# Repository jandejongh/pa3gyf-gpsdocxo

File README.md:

# pa3gyf-gpsdocxo
GPS-Disciplined OCXO

After (a.o.) G3RUH and G4HUP, with PA3GYF additions for monitoring GPS (FIX) status, extra isolation of the (sine) output signals from the PLL, monitoring OCXO heater, monitoring PLL LOCK status, manual frequency tuning (stand-alone OCXO) and stand-alone GPS operation.
Includes front and rear panel designs (Schaeffer Front-Panel Designer) and Arduino firmware,
both for Arduino Uno and Arduino Micro.

## Background

At around 2016, I decided to pick up my RF electronics and HAM hobby again after a decade (at least) absence,
and I decided to build a GPS-disciplined OCXO in order to regain lost skills.
I wanted a precision frequency reference and had struggled for years with a DCF77 circuit that never
seemed to lock. As I was able to purchase a large amount of (HP) test equipment (around 2013),
a stable frequency reference turned out to be the ideal restart project for me.

I designed and built most of the circuit in 2016 and early 2017, but never took the time to
properly test and document it. As an autumn 2019 winter project, I finished latest testing and modifications,
wrote the documentation
and submitted everything to github (before that, the repo contained photos only).

## Credits

The core design of this project, the PLL circuitry including the loop filter, was shamelessly stolen
from G3RUH; the distribution amplifier is an unmodified unit (bought) from G4HUP.

My main (modest) contributions have been the extension of the core design with monitoring and control functions,
such as monitoring whether or not the GPS receiver has a fix,
monitoring the lock status of the PLL,
RS-232C interfacing to the GPS receiver,
front-panel and rear-panel designs,
and Arduino firmware code, including an algorithm for deciding upon PLL-lock
from monitoring the OCXO tune voltage.

In addition, I changed (improved?) the interfacing between the OCXO and the PLL by
introducing an isolator for separation of the PLL and output signals from the OCXO,
and designed and implemented a Low-Noise Amplifier for the OCXO signal in case (well, almost always)
the OCXO is insufficient to properly activate the Schmitt-Triggers of the PLL circuit.

My explicit thank-yous to Frank van Vliet for his interest in this project.

## Structure of the Repository

The repository is organized as follows:
- doc:           Contains documentation; mandatory reading (in particular the 'manual')
                   if you want to rebuilt this project,
                   or use it as a basis for your own design.
                 Most if not all documentation is written with OpenOffice,
                   but I try to keep a set of PDFs in sync,
                   for those that cannot use OpenOffice.
- fpd:           Contains the front and rear panel designs (for Schaeffer, www.schaeffer-ag.de, front-panel designer).
- fw:            Contains the Arduino firmware; a single file for both Uno and Micro (compile-time switch!).
- pcb:           Contains the KiCAD PCB designs for this project.
                 The PCBs were originally designed in KiCAD v3 (well, some v3),
                   and I migrated the crucial ones (part of V1) to KiCAD v4.
- pcb/v1-kicad3: Contains the (original) KiCAD-V3xx PCB designs for all PCBs,
                   including earlier versions that had faults,
                   and including the ones for the Arduino Uno.
                 The KiCAD projects also contain a lot of 3D shape definitions.
- pcb/v1-kicad4: Contains the KiCAD-V4xx PCB designs for the essential PCBs in the V1 unit.
                 It is a subset of the pcb/v1-kicad3 KiCAD projects migrated to KiCAD V4.
                 It does not include previous PCB versions nor the Arduino Uno PCBs.
                 Also, it does not include most of the 3D shapes for the 3D view.
- transformer:   Contains details on the transformer used for the Power Supply Unit.
- enclosure:     Contains details on the Velleman enclosure (I) used.

## Conclusion

Designing and realizing this project has been a true joy!

## Future

Currently, my interest has somewhat shifted towards the accuracy of power reading of my equipment,
so I do not expect updates soon.

However, it is still on my wishlist to use an ADC with higher resolution and accuracy than the Arduino
10-bit circuits in order to assess PLL lock status.
Also, I want to study the PLL status by simply counting the pulses on both
inputs over varying intervals, in order to more accurately quantify the PLL locked status (e.g., 10-4 over
the last second, 10-6 over the past 10 minutes, 10-7 over the past hour, etc.).
I would also love to improve the RS232-C circuit in such a way that it can be used directly as an
input to Linux gpsd and ntp/chrony as a PPS-capable time source.
At the present time, this does not work.
Finally, I would love an Ethernet interface for monitoring and control of the unit.

Unfortunately, at the present time, two hurdles would need to be taken.
First, the availability of the required GPS receiver is (AFAICT) close to zero,
and I would have to switch to 1PPS use.
Second, the memory availability on the current Arduino models is really WAY TOO LOW.
I almost forgot what the K symbol means in a computer-memory context.

So, all in all, it might be better to wait for more powerful Arduino models,
and perhaps think of a 1 PPS design.

Who knows...

## License

All my parts, both hardware and software, have been released under Apache Commons License V2.

## 73

Jan (pa3gyf)

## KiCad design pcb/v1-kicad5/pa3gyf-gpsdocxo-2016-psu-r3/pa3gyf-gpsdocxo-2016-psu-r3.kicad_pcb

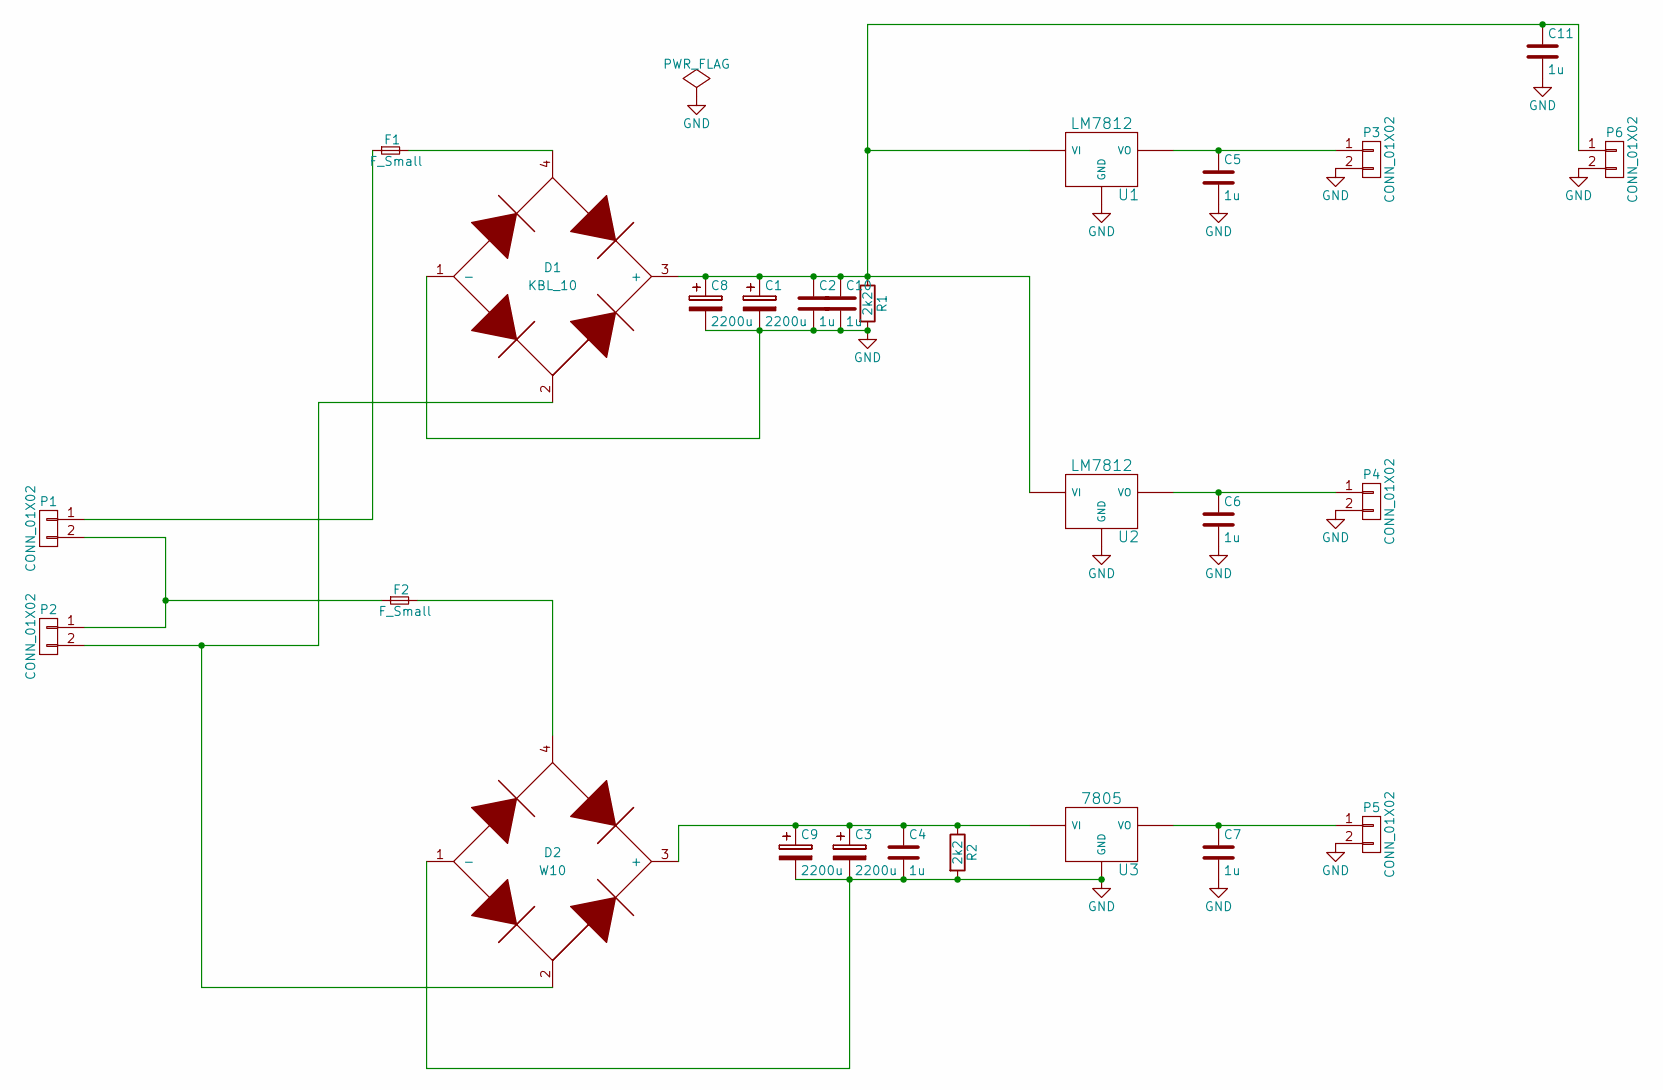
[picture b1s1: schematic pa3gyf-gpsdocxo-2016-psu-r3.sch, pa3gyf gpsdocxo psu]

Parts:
C1, C3, C8, C9: 2200u; Elko_vert_30x16mm_RM7.5
C2, C4, C5, C6, C7, C10, C11: 1u; C_0805_HandSoldering
D1: KBL_10; Bridge_KBL
D2: W10
F1, F2: F_Small; Fuseholder5x20_horiz_SemiClosed_Casing10x25mm
P1, P2, P3, P4, P5, P6: CONN_01X02; Weidmuller_GS5_2_2pin
R1, R2: 2k2; Resistor_Horizontal_RM15mm
U1, U2: LM7812; LM78XXV
U3: 7805; LM78XXV

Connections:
GND: C1.2, C2.2, C3.2, C4.2, C5.2, C6.2, C7.2, C8.2, C9.2, C10.2, C11.2, D1.1 (-), D2.1 (-), P3.2, P4.2, P5.2, P6.2, R1.2, R2.2, U1.GND, U2.GND, U3.GND
unnamed: C1.1, C2.1, C8.1, C10.1, C11.1, D1.3 (+), P6.1, R1.1, U1.VI, U2.VI
unnamed: C3.1, C4.1, C9.1, D2.3 (+), R2.1, U3.VI
unnamed: C5.1, P3.1, U1.VO
unnamed: C6.1, P4.1, U2.VO
unnamed: C7.1, P5.1, U3.VO
unnamed: D1.2, D2.2, P2.2
unnamed: D1.4, F1.2
unnamed: D2.4, F2.2
unnamed: F1.1, P1.1
unnamed: F2.1, P1.2, P2.1

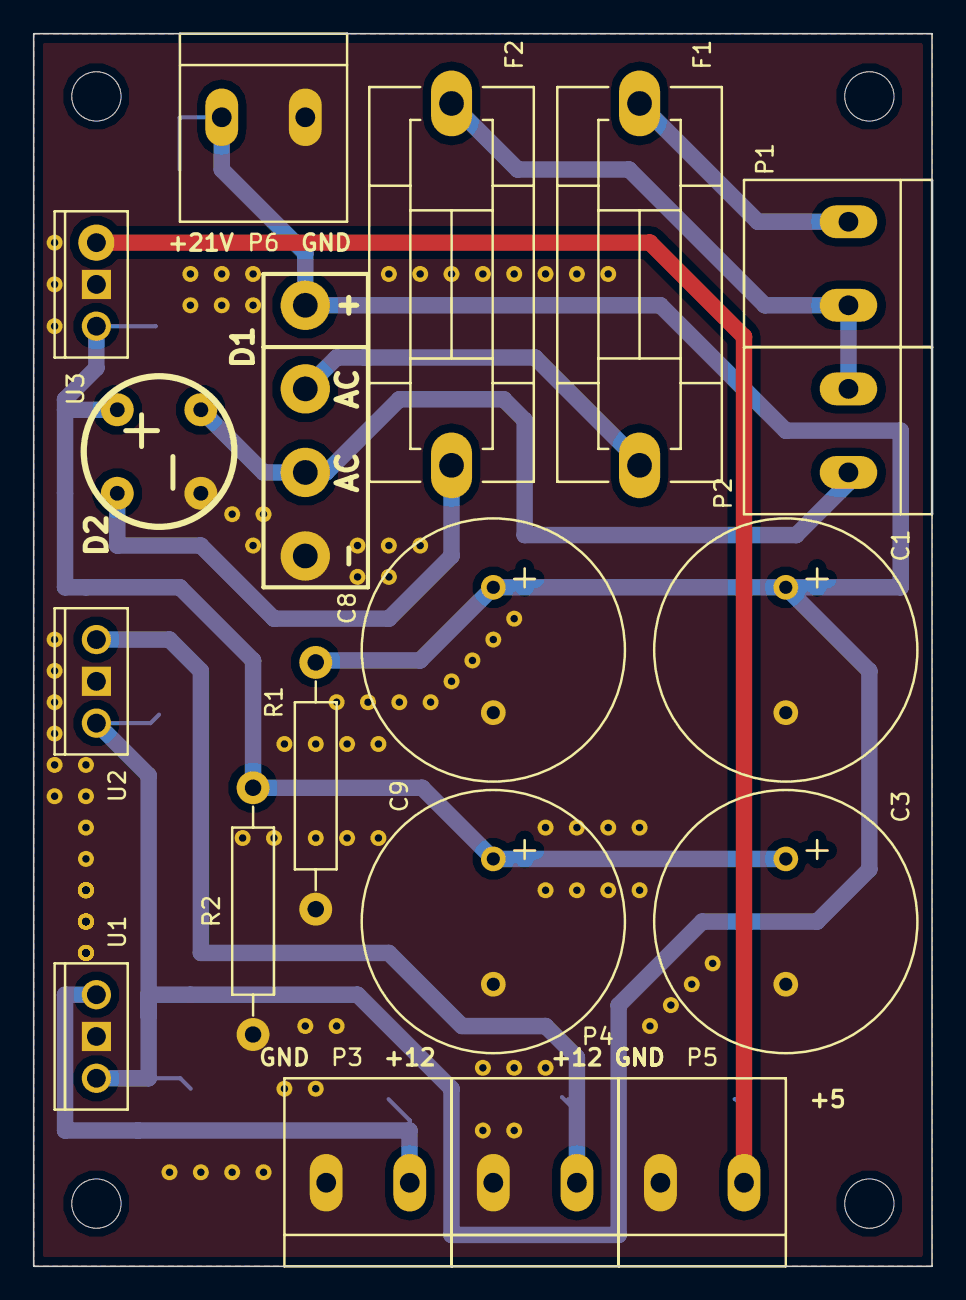
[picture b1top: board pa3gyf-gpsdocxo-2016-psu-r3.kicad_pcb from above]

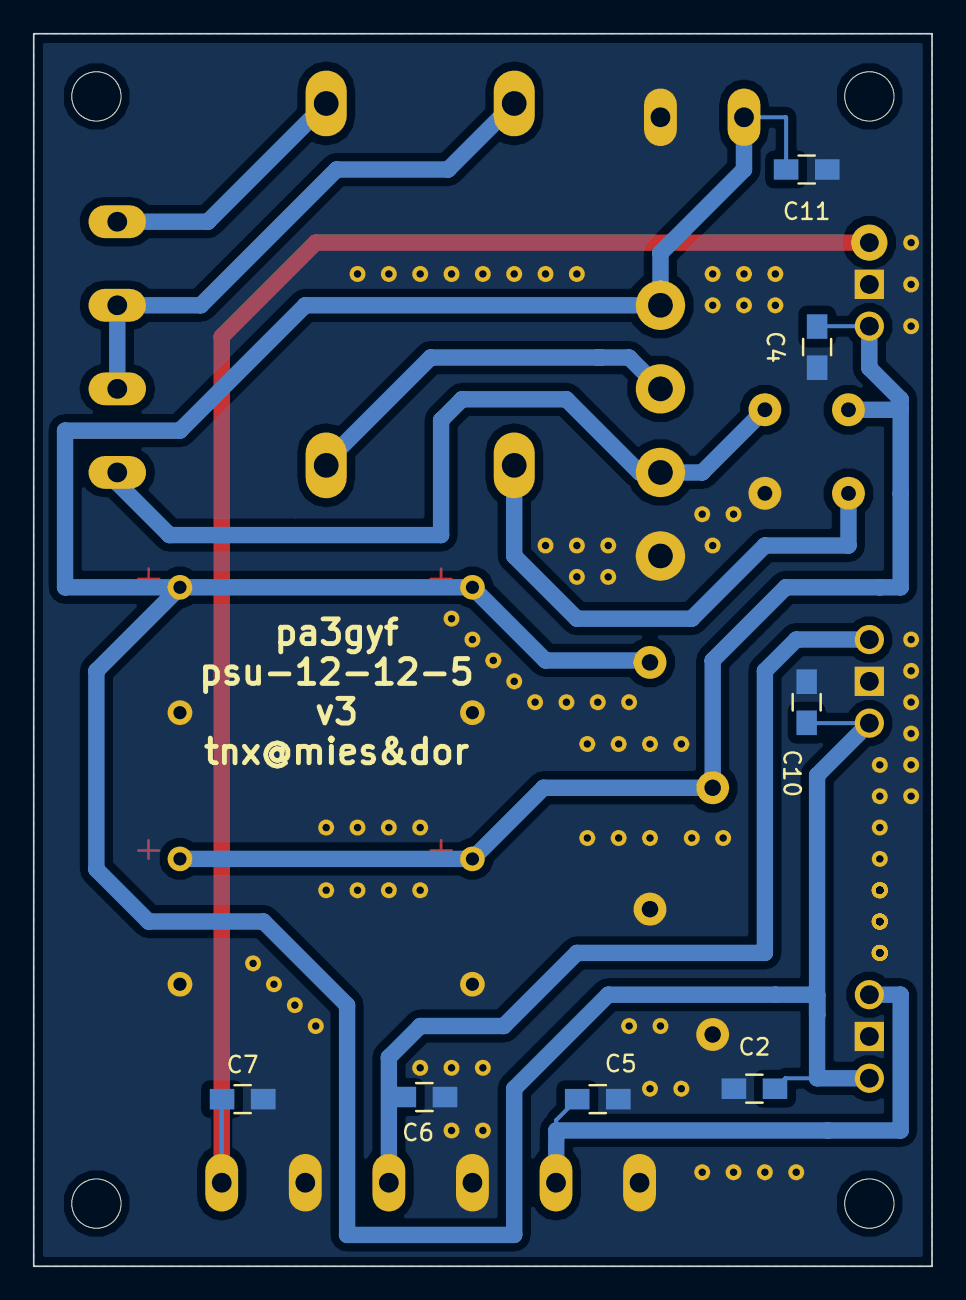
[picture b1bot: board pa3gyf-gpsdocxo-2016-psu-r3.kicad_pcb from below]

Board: 2 copper layers, 54.6 x 74.9 mm, 26 parts (7 on the bottom side), 11 nets.

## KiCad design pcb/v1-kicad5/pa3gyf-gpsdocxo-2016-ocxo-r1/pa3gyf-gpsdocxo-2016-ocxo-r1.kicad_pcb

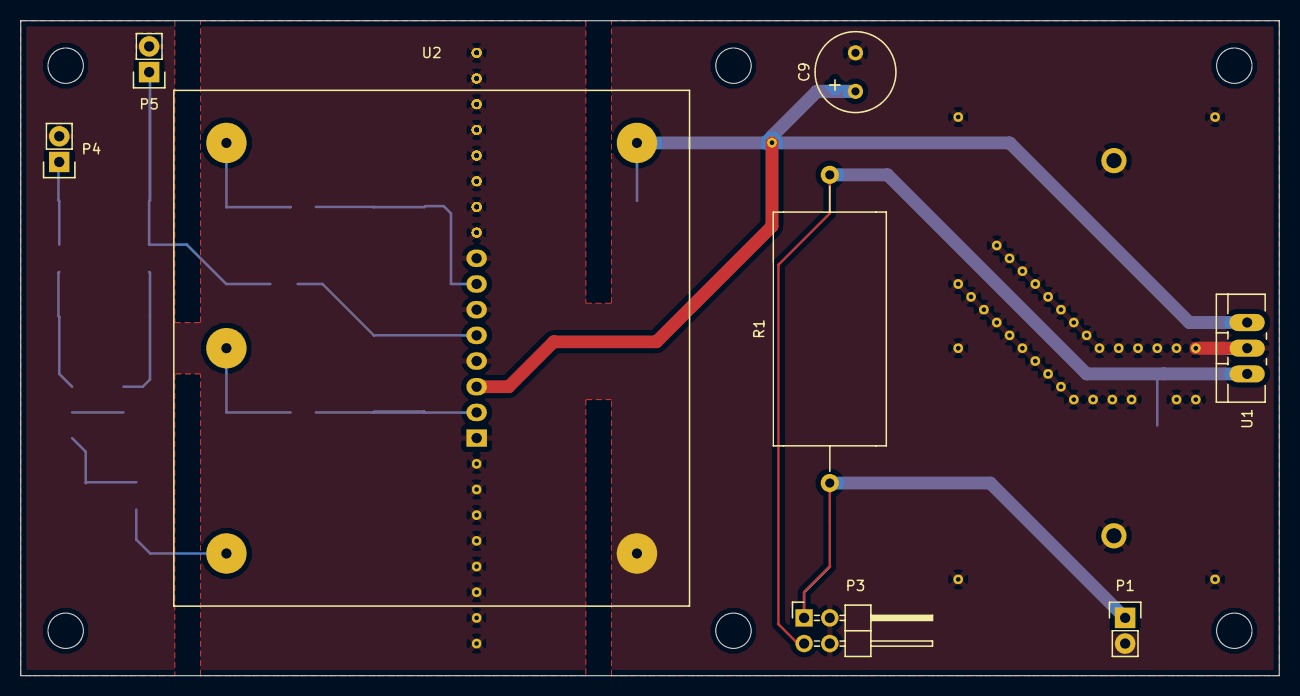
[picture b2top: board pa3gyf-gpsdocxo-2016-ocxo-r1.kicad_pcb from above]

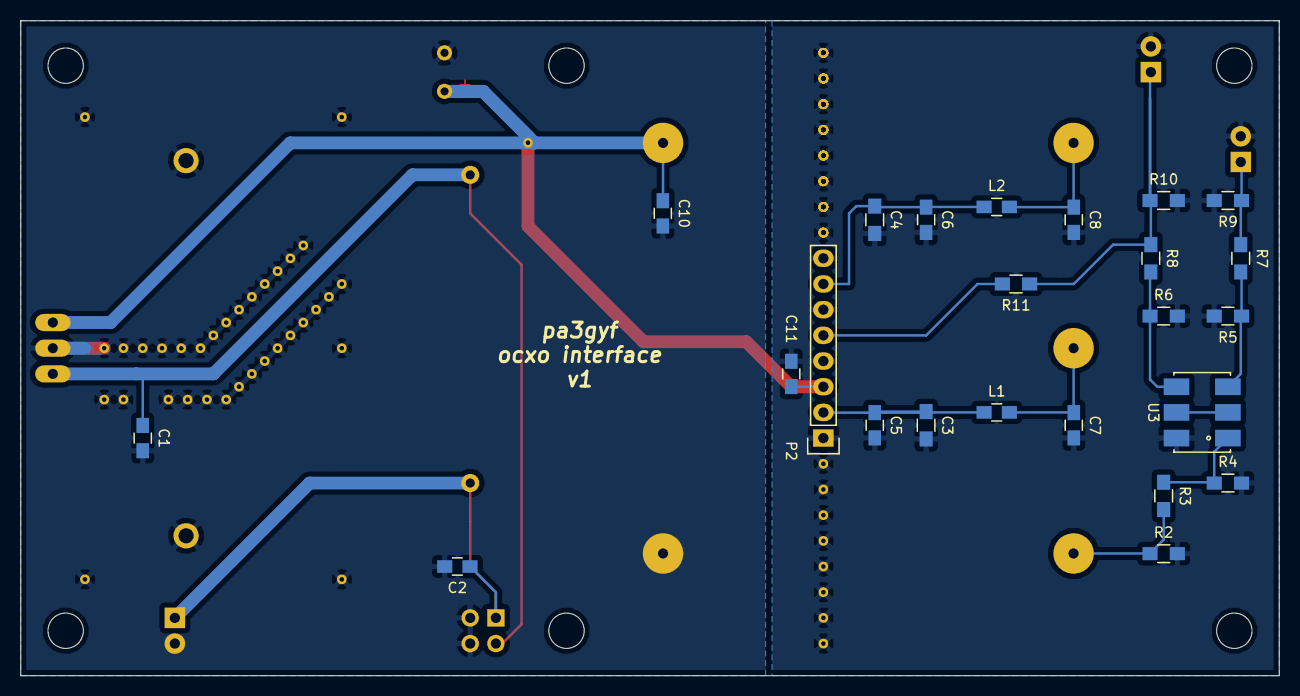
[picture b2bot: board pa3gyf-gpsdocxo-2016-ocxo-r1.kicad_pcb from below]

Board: 2 copper layers, 124.5 x 64.8 mm, 32 parts (24 on the bottom side), 16 nets.

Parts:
C1, C2, C10, C11: 1u; C_0805_HandSoldering
C3, C4: 10u; R_0805_HandSoldering
C5, C6, C7, C8: 1n; C_0805_HandSoldering
C9: 100u; Elko_vert_11.5x8mm_RM3.5
L1, L2: 22uH; C_0805_HandSoldering
P1: CONN_OCXO_UREG; Pin_Header_Straight_1x02
P2: CONN_01X08; Socket_Strip_Straight_1x08
P3: CONN_PWR_MON; Pin_Header_Angled_2x02
P4: CONN_OCXO_RF_1; Pin_Header_Straight_1x02
P5: CONN_OCXO_RF_2; Pin_Header_Straight_1x02
R1: 2R/5W; Resistor_Ceramic_Horizontal_L23mm-W9mm-H9mm-p30mm
R2, R4, R5, R6, R9, R10, R11: InfR; R_0805_HandSoldering
R3, R7, R8: 0R; R_0805_HandSoldering
U1: 78S12; TO-220_Neutral123_Vertical_LargePads
U2: MV89
U3: ADP-2-1; CD636

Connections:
78S12_IN: C1.1, P3.3, R1.2, U1.1
78S12_OUT: C9.1, C10.1, C11.1, P2.3, U1.3, U2.5
GND: C1.2, C2.2, C3.2, C4.2, C5.2, C6.2, C7.2, C8.2, C9.2, C10.2, C11.2, P1.2, P2.1, P2.4, P2.6, P2.8, P3.2, P3.4, P4.2, P5.2, R2.2, R4.2, R5.2, R6.2, R9.2, R10.2, U1.2, U2.4, U3.6
unnamed: C2.1, P1.1, P3.1, R1.1
unnamed: R5.1, R7.2, U3.3
unnamed: R6.1, R8.2, U3.4
unnamed: U3.2, U3.5
OCXO_RF: R2.1, R3.2, U2.3
OCXO_RF_1: P4.1, R7.1, R9.1
OCXO_RF_2: P5.1, R8.1, R10.1, R11.1
OCXO_RF_MATCHED: R3.1, R4.1, U3.1
OCXO_RF_PLL: P2.5, R11.2
OCXO_TUNE: C8.1, L2.2, U2.1
OCXO_TUNE_PLL: C4.1, C6.1, L2.1, P2.7
OCXO_VREF: C7.1, L1.2, U2.2
OCXO_VREF_PLL: C3.1, C5.1, L1.1, P2.2

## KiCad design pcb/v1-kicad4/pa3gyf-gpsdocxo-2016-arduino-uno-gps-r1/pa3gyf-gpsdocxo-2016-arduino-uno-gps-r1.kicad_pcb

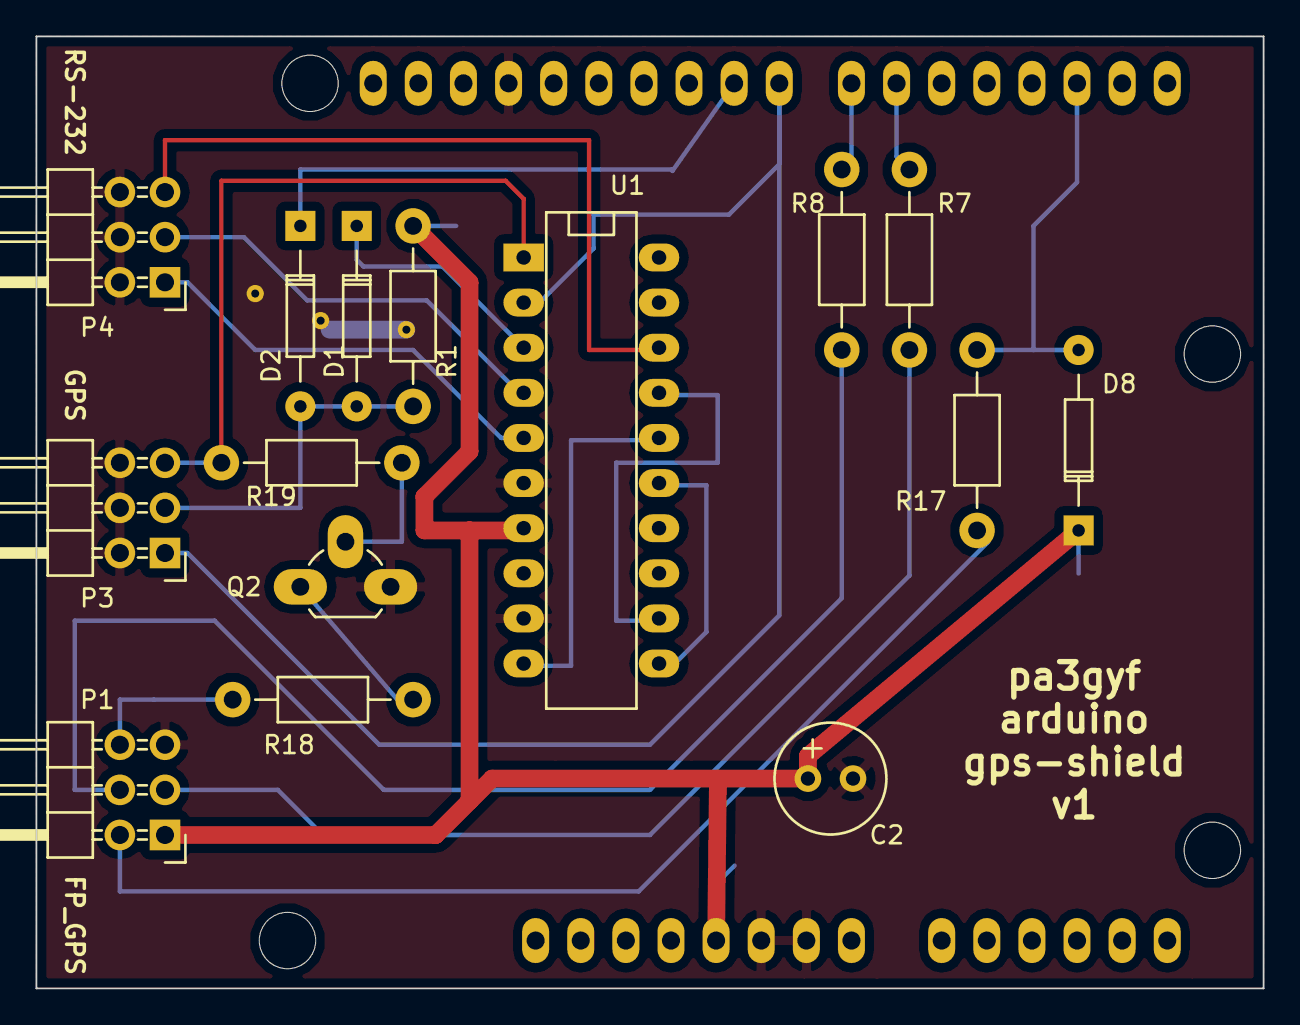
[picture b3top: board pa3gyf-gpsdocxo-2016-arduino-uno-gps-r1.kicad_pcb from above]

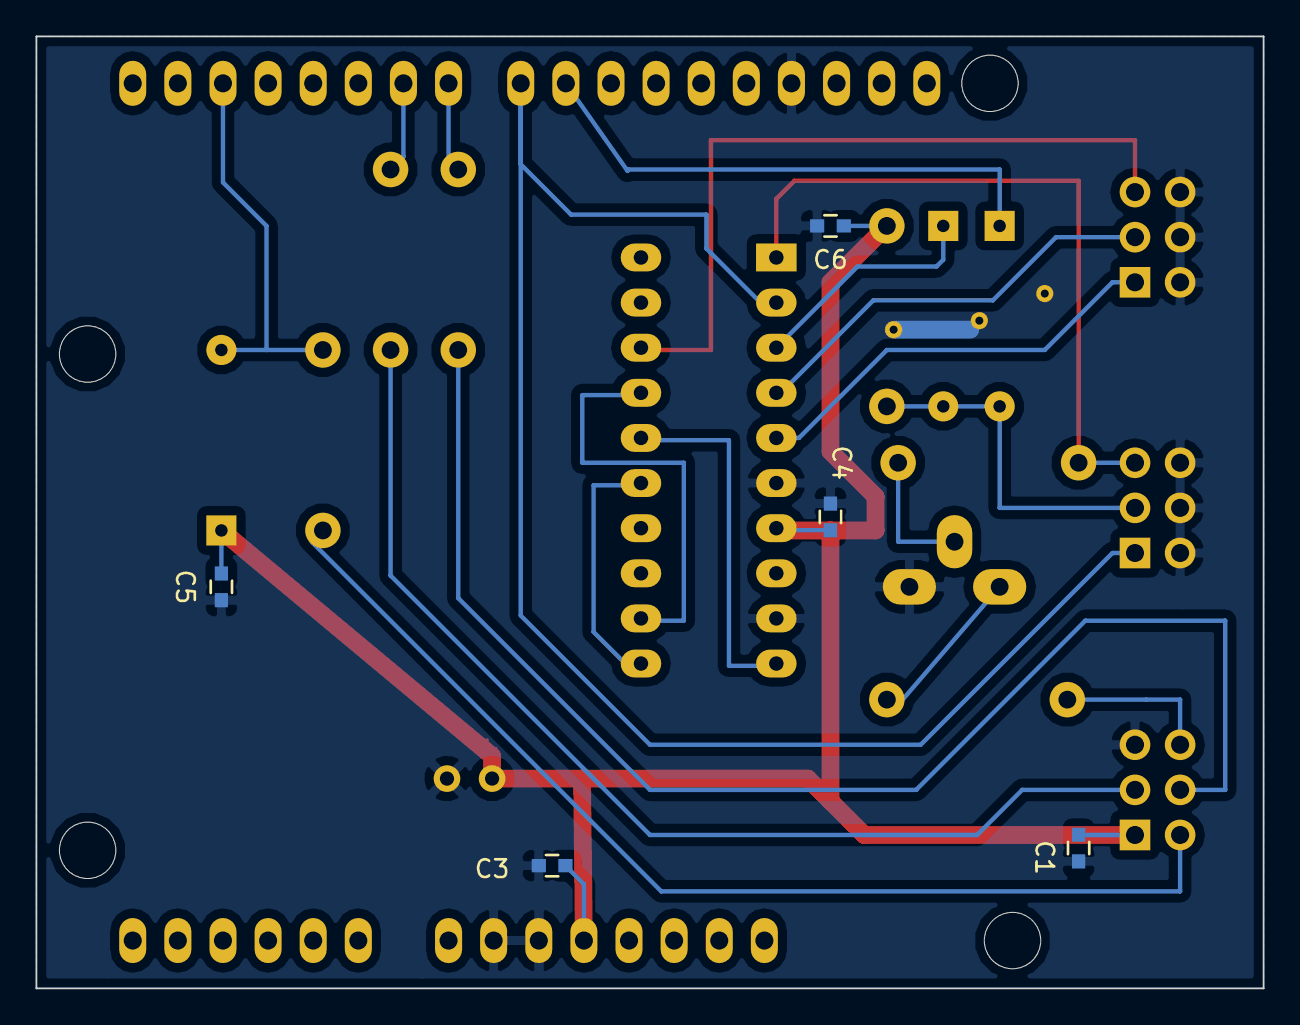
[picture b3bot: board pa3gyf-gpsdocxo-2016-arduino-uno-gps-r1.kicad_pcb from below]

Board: 2 copper layers, 69.1 x 53.6 mm, 21 parts (5 on the bottom side), 22 nets.

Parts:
C1, C3, C4, C5, C6: 1u; C_0603
C2: 22u; Elko_vert_11.2x6.3mm_RM2.5
D1, D2, D8: 1N4148; Diode_DO-35_SOD27_Horizontal_RM10
P1: CONN_FP_GPS; Pin_Header_Angled_2x03
P3: CONN_GPS_RS232; Pin_Header_Angled_2x03
P4: CONN_BP_RS232; Pin_Header_Angled_2x03
Q2: BC547; TO-92_Rugged
R1, R19: 4k7; Resistor_Horizontal_RM10mm
R7, R8, R18: 270R; Resistor_Horizontal_RM10mm
R17: 1k; Resistor_Horizontal_RM10mm
SHIELD1: ARDUINO_SHIELD
U1: MAX233_DIP; DIP-20__300_ELL

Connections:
+5V: C1.1, C2.1, C3.1, C4.1, C5.1, C6.1, D8.2, P1.1, R1.1, SHIELD1.5V, U1.7
GND: C1.2, C2.2, C3.2, C4.2, C5.2, C6.2, P1.5, P3.2, P3.4, P3.6, P4.2, P4.4, P4.6, Q2.3, SHIELD1.GND1, SHIELD1.GND2, SHIELD1.GND3, U1.6, U1.9
unnamed: D2.2, SHIELD1.9
unnamed: D8.1, R17.1, SHIELD1.2
unnamed: P1.2, R17.2
unnamed: P1.3, R8.1
unnamed: P1.4, R7.1
unnamed: P1.6, R18.2
unnamed: Q2.1, R18.1
unnamed: Q2.2, R19.2
unnamed: R7.2, SHIELD1.7
unnamed: R8.2, SHIELD1.6
unnamed: U1.10, U1.16
unnamed: U1.11, U1.15
unnamed: U1.12, U1.17
gps_pps: P3.5, R19.1, U1.1
gps_rx: D1.1, D2.1, P3.3, R1.2
gps_tx: P3.1, SHIELD1.8, U1.2
rs232_dce_dcd: P4.5, U1.18
rs232_dce_rxd: P4.1, U1.5
rs232_dce_txd: P4.3, U1.4
rs232_dte_txd_ttl: D1.2, U1.3

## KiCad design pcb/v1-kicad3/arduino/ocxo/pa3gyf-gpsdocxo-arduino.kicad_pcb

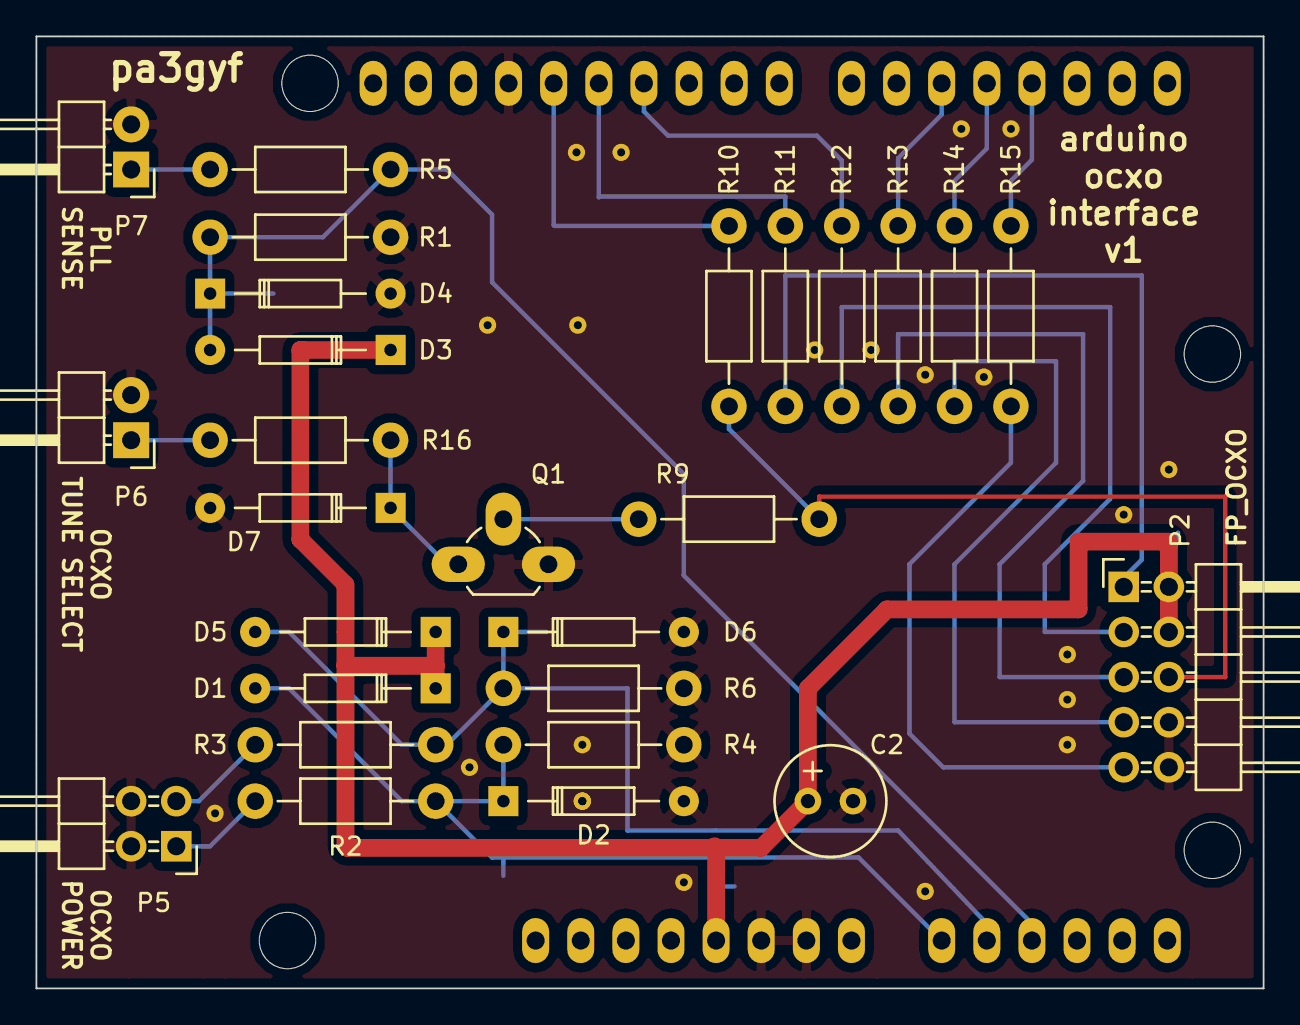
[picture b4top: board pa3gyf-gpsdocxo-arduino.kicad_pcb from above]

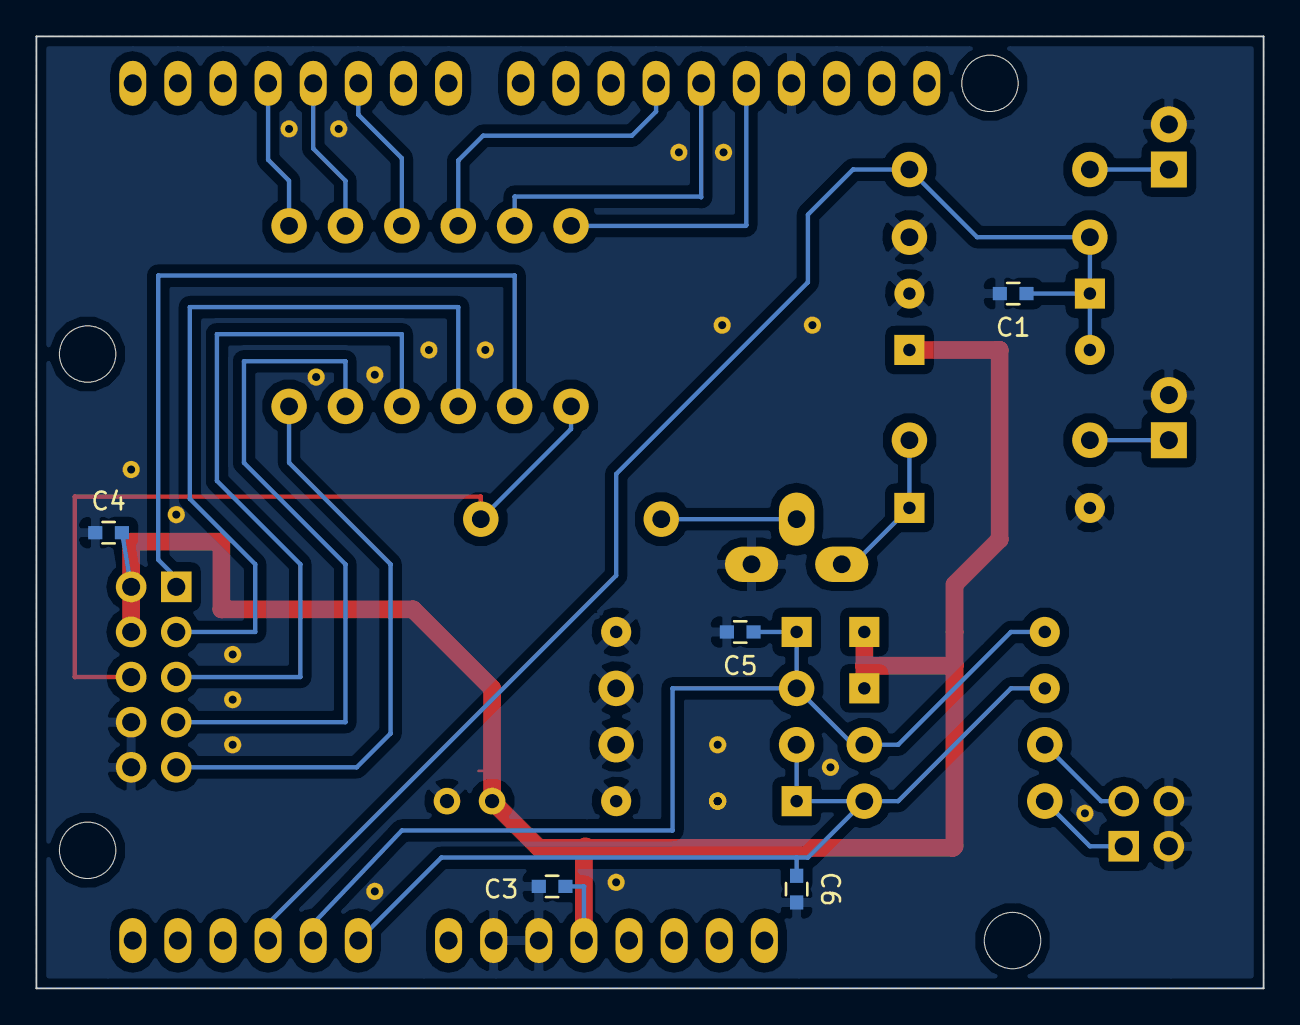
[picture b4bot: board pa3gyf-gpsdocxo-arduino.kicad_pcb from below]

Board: 2 copper layers, 69.1 x 53.6 mm, 33 parts (5 on the bottom side), 23 nets.

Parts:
C1, C3, C4, C5, C6: 1u; C_0603
C2: 22u; Elko_vert_11.2x6.3mm_RM2.5
D1, D2, D3, D4, D5, D6, D7: 1N4148; Diode_DO-35_SOD27_Horizontal_RM10
P2: CONN_FP_OCXO; Pin_Header_Angled_2x05
P5: CONN_OCXO_POWER; Pin_Header_Angled_2x02
P6: CONN_OCXO_TUNE_SELECT; Pin_Header_Angled_1x02
P7: CONN_PLL_SENSE; Pin_Header_Angled_1x02
Q1: BC547; TO-92_Rugged
R1: 1k; Resistor_Horizontal_RM10mm
R2, R3, R5, R9, R10: 10k; Resistor_Horizontal_RM10mm
R4, R6: 2k2; Resistor_Horizontal_RM10mm
R11, R12, R13, R14, R15: 270R; Resistor_Horizontal_RM10mm
R16: 100; Resistor_Horizontal_RM10mm
SHIELD1: ARDUINO_SHIELD

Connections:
+5V: C2.1, C3.1, C4.1, D1.2, D3.2, D5.2, P2.2, P2.4, SHIELD1.5V
GND: C1.2, C2.2, C3.2, C4.2, C5.2, C6.2, D2.1, D4.1, D6.1, D7.1, P2.8, P2.10, P5.2, P5.4, P6.2, P7.2, Q1.3, R4.2, R5.2, R6.2, SHIELD1.GND1, SHIELD1.GND2, SHIELD1.GND3
unnamed: C1.1, D3.1, D4.2, R1.1, R5.1, SHIELD1.AD2
unnamed: C5.1, D5.1, D6.2, R3.1, R6.1, SHIELD1.AD1
unnamed: C6.1, D1.1, D2.2, R2.1, R4.1, SHIELD1.AD0
unnamed: D7.2, Q1.1, R16.2
unnamed: P5.1, R2.2
unnamed: P5.3, R3.2
unnamed: P7.1, R1.2
unnamed: Q1.2, R9.2
unnamed: R10.2, SHIELD1.13
unnamed: R11.2, SHIELD1.12
unnamed: R12.2, SHIELD1.11
unnamed: R13.2, SHIELD1.5
unnamed: R14.2, SHIELD1.4
unnamed: R15.2, SHIELD1.3
heater_green: P2.3, R12.1
heater_red: P2.1, R11.1
locked_green: P2.7, R14.1
locked_red: P2.5, R13.1
tune_man: P2.9, R15.1
tune_pll: P6.1, R16.1
tune_sel: P2.6, R9.1, R10.1

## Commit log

2016-12-09 Add files via upload
    Added some photos.
2019-10-06 Committing from local wotking directory.
2019-10-06 Added file.
2019-10-06 Added note on the enclosure.
2019-10-06 Restructured fw directory.
2019-10-06 Renamed fw file.
2019-10-06 Renamed fw file (again).
2019-10-08 Updated doc.
2019-10-14 Progress on documentation and archiving KiCAD projects.
2019-10-14 Added Jupiter GPS Manual.
2019-10-23 Progress on v1 documentation and started v2 design.
2021-03-02 New pictures and changes to manual.
2021-03-02 Committing apparent changes in working directory.
